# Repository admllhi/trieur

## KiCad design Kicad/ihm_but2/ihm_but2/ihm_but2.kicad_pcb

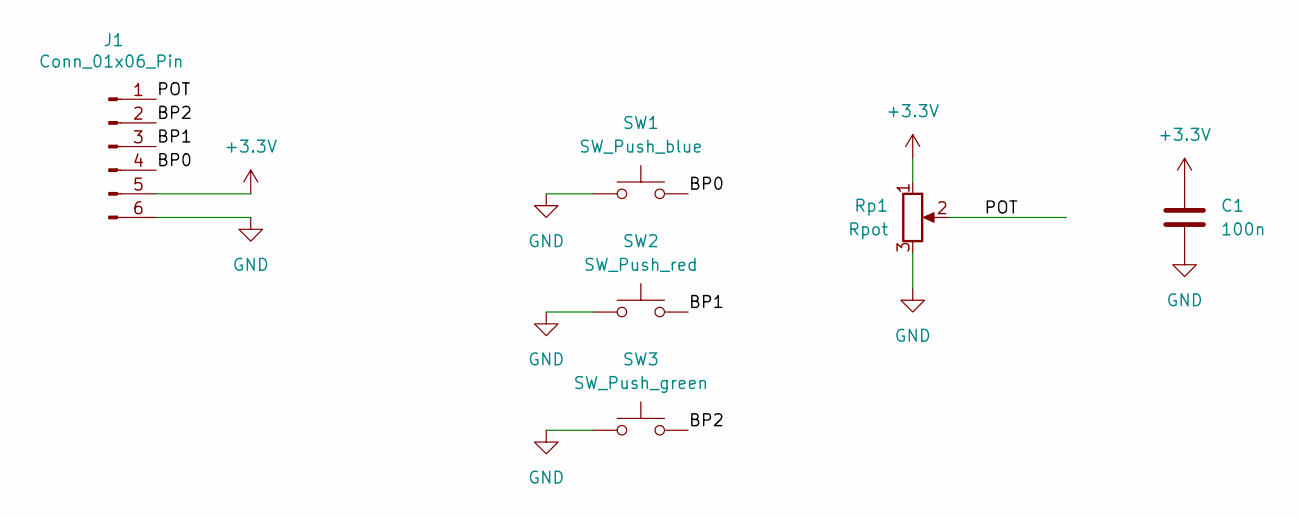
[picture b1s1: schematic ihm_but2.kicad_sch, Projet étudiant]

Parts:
C1: 100n; C_Rect_L7.0mm_W2.5mm_P5.00mm
J1: Conn_01x06_Pin; PinHeader_1x06_P2.54mm_Horizontal
Rp1: Rpot; 63M_1
SW1: SW_Push_blue; SW_PUSH_5mm_blue
SW2: SW_Push_red; SW_PUSH_5mm_red
SW3: SW_Push_green; SW_PUSH_5mm_green

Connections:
+3.3V: C1.1, J1.5, Rp1.1
/BP0: J1.4, SW1.2
/BP1: J1.3, SW2.2
/BP2: J1.2, SW3.2
/POT: J1.1, Rp1.2
GND: C1.2, J1.6, Rp1.3, SW1.1, SW2.1, SW3.1

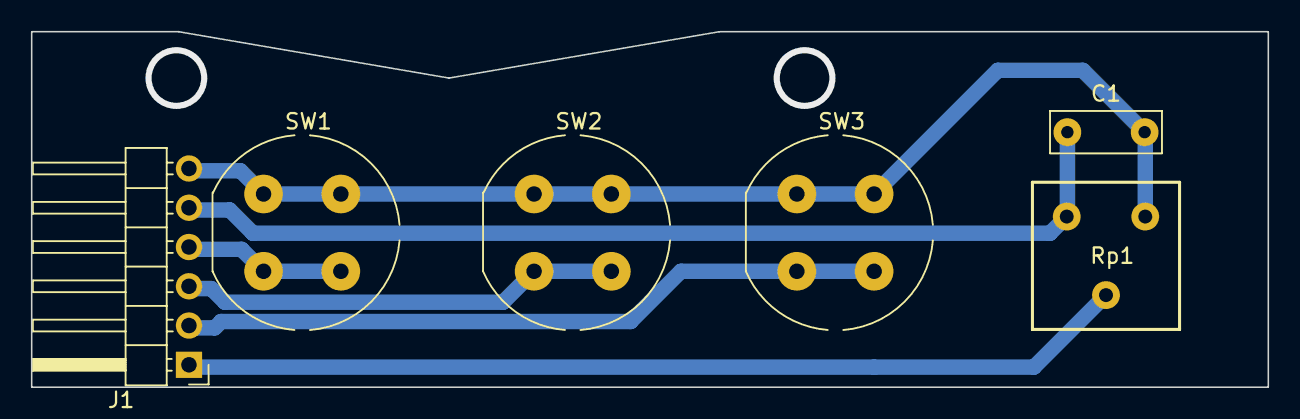
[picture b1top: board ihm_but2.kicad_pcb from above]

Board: 2 copper layers, 80.0 x 23.0 mm, 6 parts (0 on the bottom side), 6 nets.

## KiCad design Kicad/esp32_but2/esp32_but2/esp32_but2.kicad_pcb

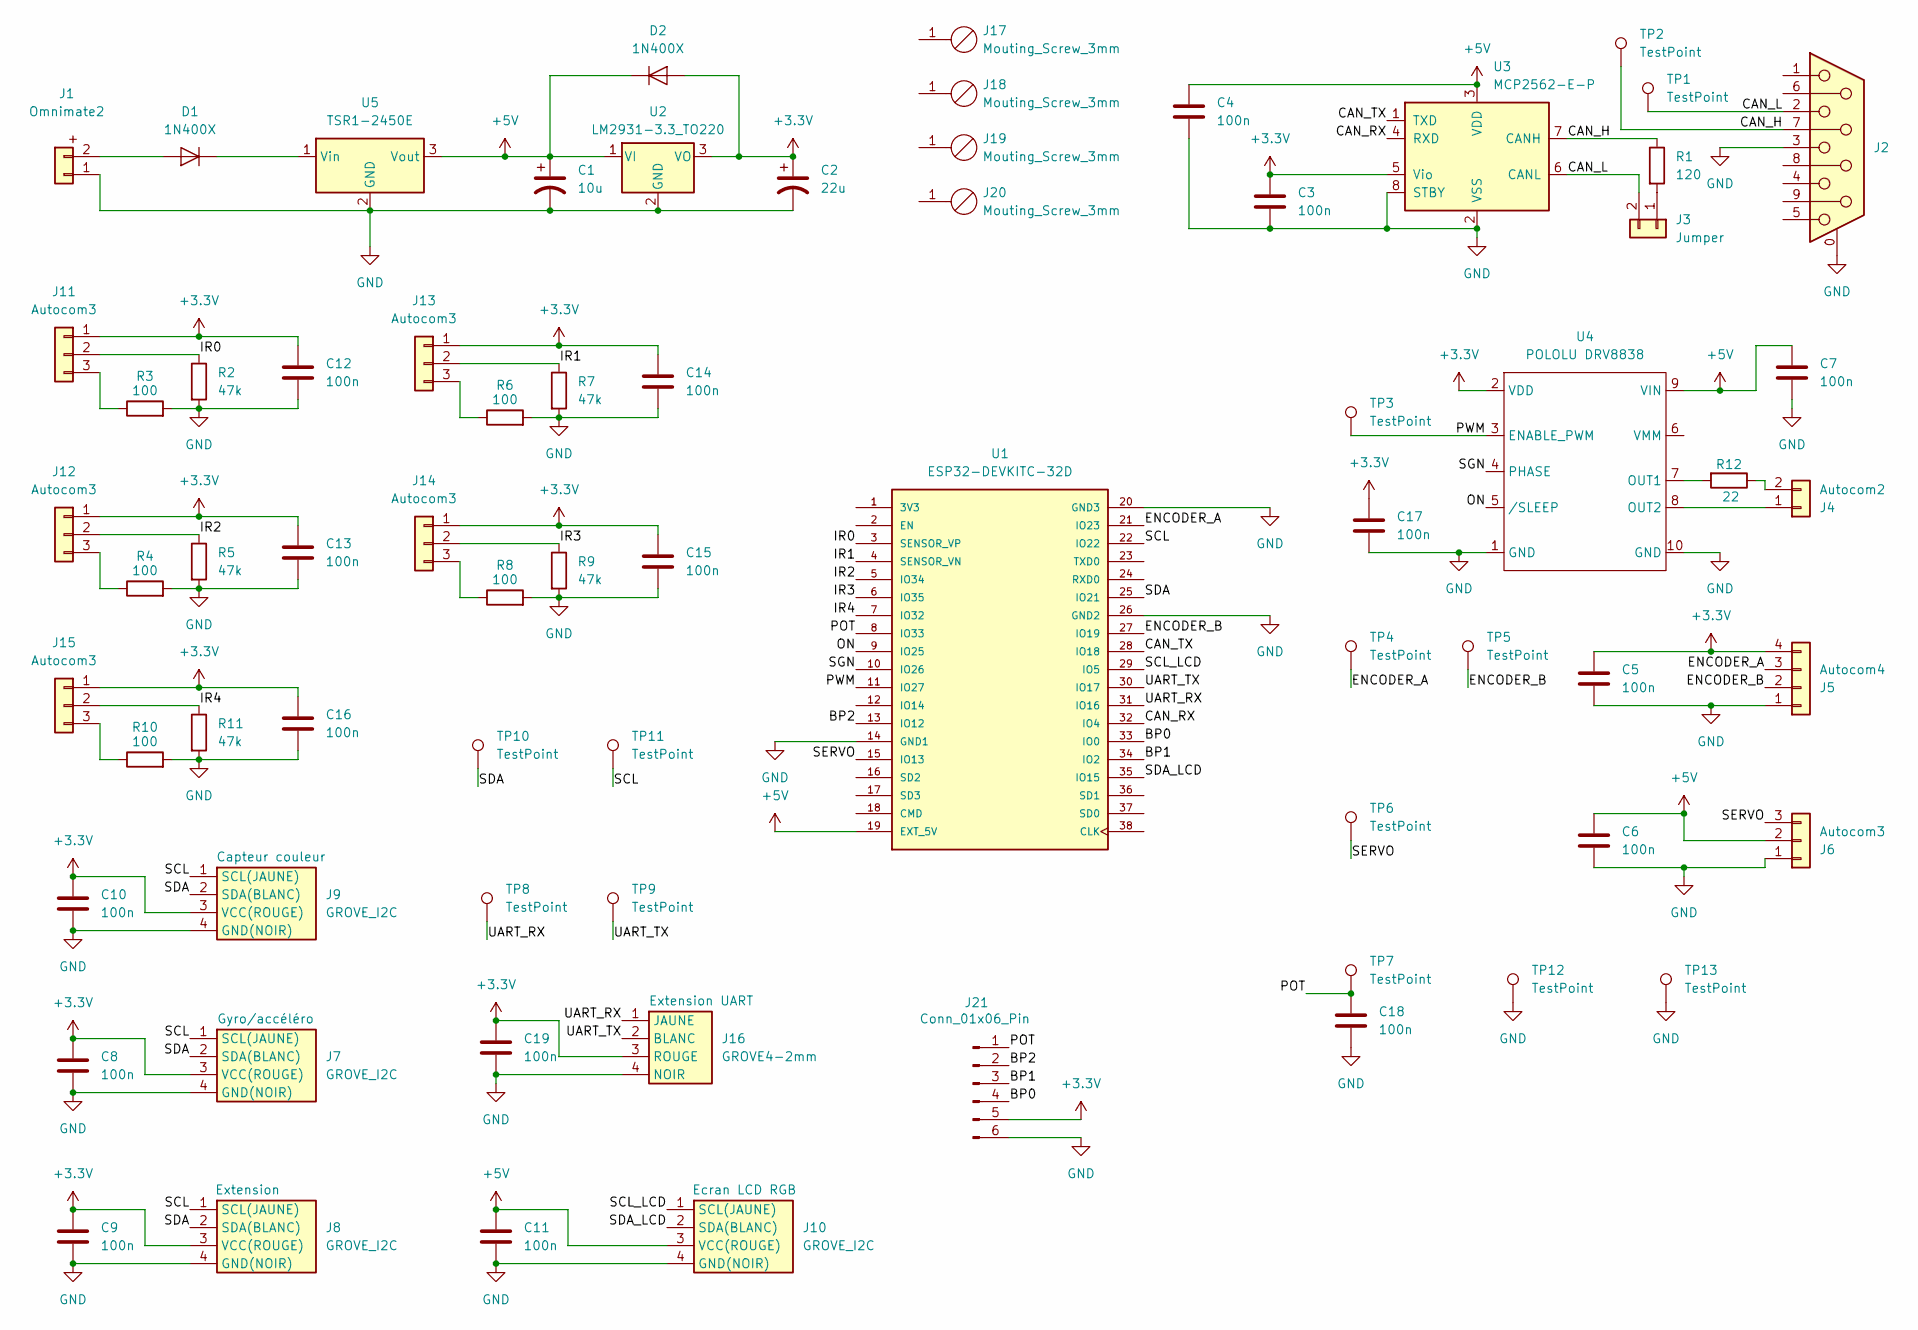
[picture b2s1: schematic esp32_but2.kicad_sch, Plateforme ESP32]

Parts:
C1: 10u; C_Rect_L7.0mm_W2.5mm_P5.00mm
C2: 22u; C_Rect_L7.0mm_W2.5mm_P5.00mm
C3, C4, C5, C6, C7, C8, C9, C10, C11, C12, C13, C14, C15, C16, C17, C18, C19: 100n; C_Rect_L7.0mm_W2.5mm_P5.00mm
D1, D2: 1N400X; D_DO-41_SOD81_P10.16mm_Horizontal
J1: Omnimate2; OmnimateSL-5,08_1x02_P5.08mm_Vertical
J2: DE9_Receptacle_MountingHoles; DSUB-9_Female_Horizontal_P2.77x2.84mm_EdgePinOffset4.94mm_H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
J3: Jumper; PinHeader_1x02_P2.54mm_Vertical
J4: Autocom2
J5: Autocom4
J6, J11, J12, J13, J14, J15: Autocom3
J7, J8, J9, J10: GROVE_I2C; SEEED_110990030
J16: GROVE4-2mm; SEEED_110990030
J17, J18, J19, J20: Mouting_Screw_3mm; Mounting_Screw_3mm
J21: Conn_01x06_Pin; PinHeader_1x06_P2.54mm_Vertical
R1: 120; R_Axial_DIN0207_L6.3mm_D2.5mm_P10.16mm_Horizontal
R2, R5, R7, R9, R11: 47k; R_Axial_DIN0207_L6.3mm_D2.5mm_P10.16mm_Horizontal
R3, R4, R6, R8, R10: 100; R_Axial_DIN0207_L6.3mm_D2.5mm_P10.16mm_Horizontal
R12: 22; R_Axial_DIN0207_L6.3mm_D2.5mm_P10.16mm_Horizontal
TP1, TP2, TP3, TP4, TP5, TP6, TP7, TP8, TP9, TP10, TP11, TP12, TP13: TestPoint; PinHeader_1x01_P2.54mm_Vertical
U1: ESP32-DEVKITC-32D; MODULE_ESP32-DEVKITC-32D; PARTREV 4
U2: LM2931-3.3_TO220; TO-220-3_Horizontal_TabDown
U3: MCP2562-E-P; DIP-8_W7.62mm
U4: POLOLU DRV8838; POLOLU-2990
U5: TSR1-2450E; Converter_DCDC_TRACO_TSR1-xxxxE_THT

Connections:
+3.3V: C2.1, C3.1, C5.1, C8.1, C9.1, C10.1, C12.1, C13.1, C14.1, C15.1, C16.1, C17.1, C19.1, D2.2 (A), J5.4, J7.3 (VCC(ROUGE)), J8.3 (VCC(ROUGE)), J9.3 (VCC(ROUGE)), J11.1, J12.1, J13.1, J14.1, J15.1, J16.3 (ROUGE), J21.5, U2.3 (VO), U3.5 (Vio), U4.2 (VDD)
+5V: C1.1, C4.1, C6.1, C7.1, C11.1, D2.1 (K), J6.2, J10.3 (VCC(ROUGE)), U1.19 (EXT_5V), U2.1 (VI), U3.3 (VDD), U4.9 (VIN), U5.3 (Vout)
/BP0: J21.4, U1.33 (IO0)
/BP1: J21.3, U1.34 (IO2)
/BP2: J21.2, U1.13 (IO12)
/CAN_H: J2.7, R1.1, TP2.1, U3.7 (CANH)
/CAN_L: J2.2, J3.2, TP1.1, U3.6 (CANL)
/CAN_RX: U1.32 (IO4), U3.4 (RXD)
/CAN_TX: U1.28 (IO18), U3.1 (TXD)
/ENCODER_A: J5.3, TP4.1, U1.21 (IO23)
/ENCODER_B: J5.2, TP5.1, U1.27 (IO19)
/IR0: J11.2, R2.1, U1.3 (SENSOR_VP)
/IR1: J13.2, R7.1, U1.4 (SENSOR_VN)
/IR2: J12.2, R5.1, U1.5 (IO34)
/IR3: J14.2, R9.1, U1.6 (IO35)
/IR4: J15.2, R11.1, U1.7 (IO32)
/ON: U1.9 (IO25), U4.5 (/SLEEP)
/POT: C18.1, J21.1, TP7.1, U1.8 (IO33)
/PWM: TP3.1, U1.11 (IO27), U4.3 (ENABLE_PWM)
/SCL: J7.1 (SCL(JAUNE)), J8.1 (SCL(JAUNE)), J9.1 (SCL(JAUNE)), TP11.1, U1.22 (IO22)
/SCL_LCD: J10.1 (SCL(JAUNE)), U1.29 (IO5)
/SDA: J7.2 (SDA(BLANC)), J8.2 (SDA(BLANC)), J9.2 (SDA(BLANC)), TP10.1, U1.25 (IO21)
/SDA_LCD: J10.2 (SDA(BLANC)), U1.35 (IO15)
/SERVO: J6.3, TP6.1, U1.15 (IO13)
/SGN: U1.10 (IO26), U4.4 (PHASE)
/UART_RX: J16.1 (JAUNE), TP8.1, U1.31 (IO16)
/UART_TX: J16.2 (BLANC), TP9.1, U1.30 (IO17)
GND: C1.2, C2.2, C3.2, C4.2, C5.2, C6.2, C7.2, C8.2, C9.2, C10.2, C11.2, C12.2, C13.2, C14.2, C15.2, C16.2, C17.2, C18.2, C19.2, J1.1, J2.0 (PAD), J2.3, J5.1, J6.1, J7.4 (GND(NOIR)), J8.4 (GND(NOIR)), J9.4 (GND(NOIR)), J10.4 (GND(NOIR)), J16.4 (NOIR), J21.6, R2.2, R3.2, R4.2, R5.2, R6.2, R7.2, R8.2, R9.2, R10.2, R11.2, TP12.1, TP13.1, U1.14 (GND1), U1.20 (GND3), U1.26 (GND2), U2.2 (GND), U3.2 (VSS), U3.8 (STBY), U4.1 (GND), U4.10 (GND), U5.2 (GND)
unnamed: D1.2 (A), J1.2
unnamed: D1.1 (K), U5.1 (Vin)
unnamed: J3.1, R1.2
unnamed: J4.1, U4.8 (OUT2)
unnamed: J4.2, R12.1
unnamed: J11.3, R3.1
unnamed: J12.3, R4.1
unnamed: J13.3, R6.1
unnamed: J14.3, R8.1
unnamed: J15.3, R10.1
unnamed: R12.2, U4.7 (OUT1)

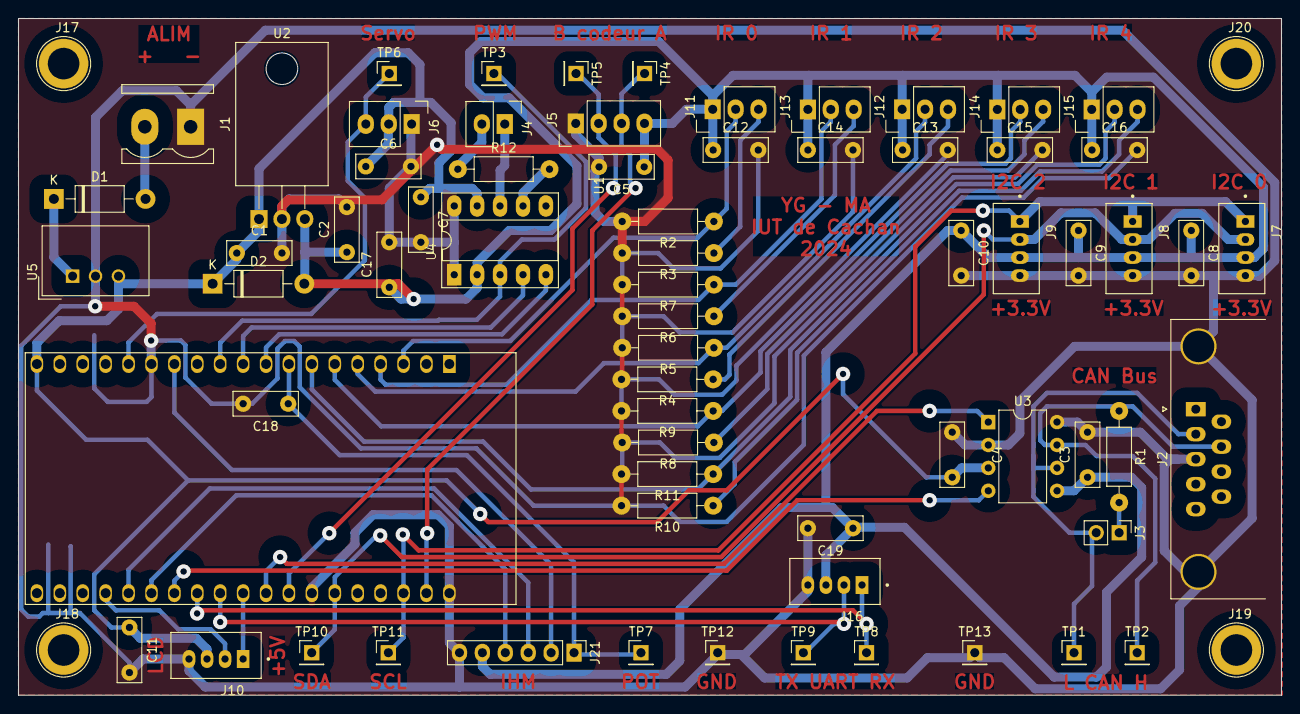
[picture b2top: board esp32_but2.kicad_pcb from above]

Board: 2 copper layers, 140.0 x 75.0 mm, 72 parts (0 on the bottom side), 39 nets.

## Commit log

2026-01-26 Potar+BP
2026-01-26 Commit V2
2026-01-30 encodeur
2026-01-30 machine a etat non finie
2026-02-02 MACHINE A ETAT
2026-02-02 fgd jgfjsd;dshb nxcdj
2026-02-05 Sujet 2 fini
2026-02-05 Machine a etat finie trie correctement
